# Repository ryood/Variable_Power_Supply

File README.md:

Variable_Power_Supply
=====================

両電源の可変電圧電源
電流電圧計付き

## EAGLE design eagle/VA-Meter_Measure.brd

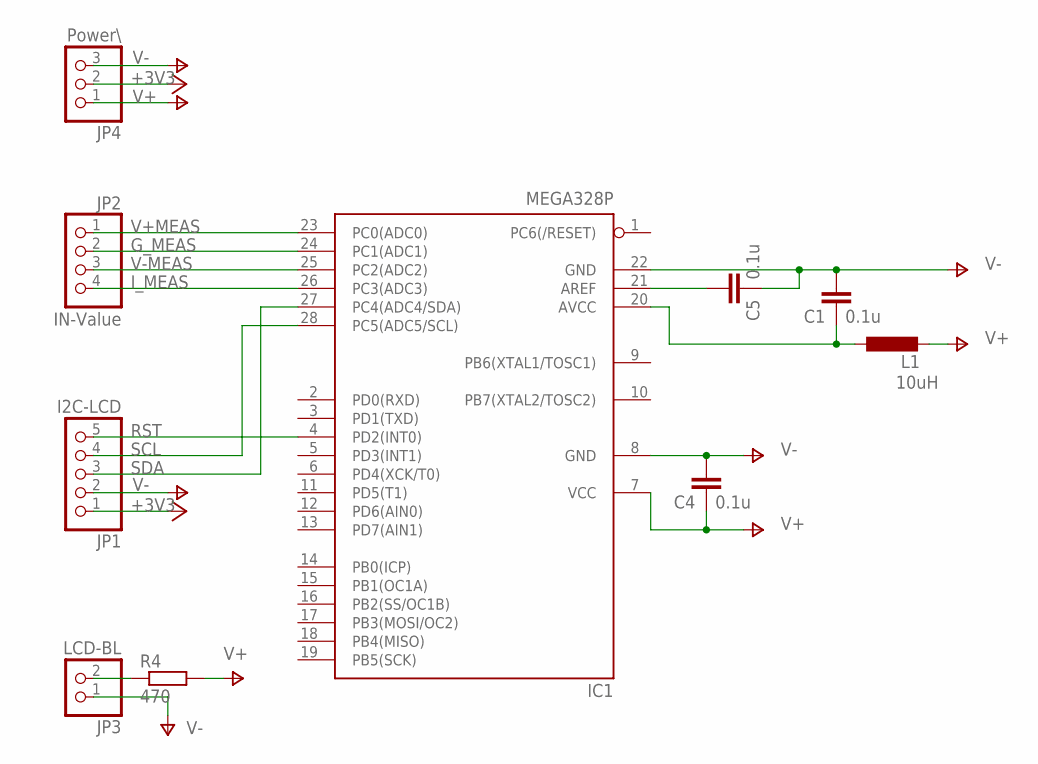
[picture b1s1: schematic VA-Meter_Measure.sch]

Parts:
C1, C4, C5: 0.1u; C050-024X044
IC1: MEGA328P
JP1: I2C-LCD; 1X05
JP2: IN-Value; 1X04
JP3: LCD-BL; 1X02
JP4: Power\; 1X03
L1: 10uH; 6000-XXXX-RC
R4: 470; 0207/7

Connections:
+3V3: JP1.1, JP4.2
G_MEAS: IC1.24 (PC1(ADC1)), JP2.2
I_MEAS: IC1.26 (PC3(ADC3)), JP2.4
unnamed: JP3.2, R4.1
unnamed: C5.2, IC1.21 (AREF)
unnamed: C1.1, IC1.20 (AVCC), L1.1
RST: IC1.4 (PD2(INT0)), JP1.5
SCL: IC1.28 (PC5(ADC5/SCL)), JP1.4
SDA: IC1.27 (PC4(ADC4/SDA)), JP1.3
V+: C4.1, IC1.7 (VCC), JP4.1, L1.2, R4.2
V+MEAS: IC1.23 (PC0(ADC0)), JP2.1
V-: C1.2, C4.2, C5.1, IC1.8 (GND), IC1.22 (GND), JP1.2, JP3.1, JP4.3
V-MEAS: IC1.25 (PC2(ADC2)), JP2.3

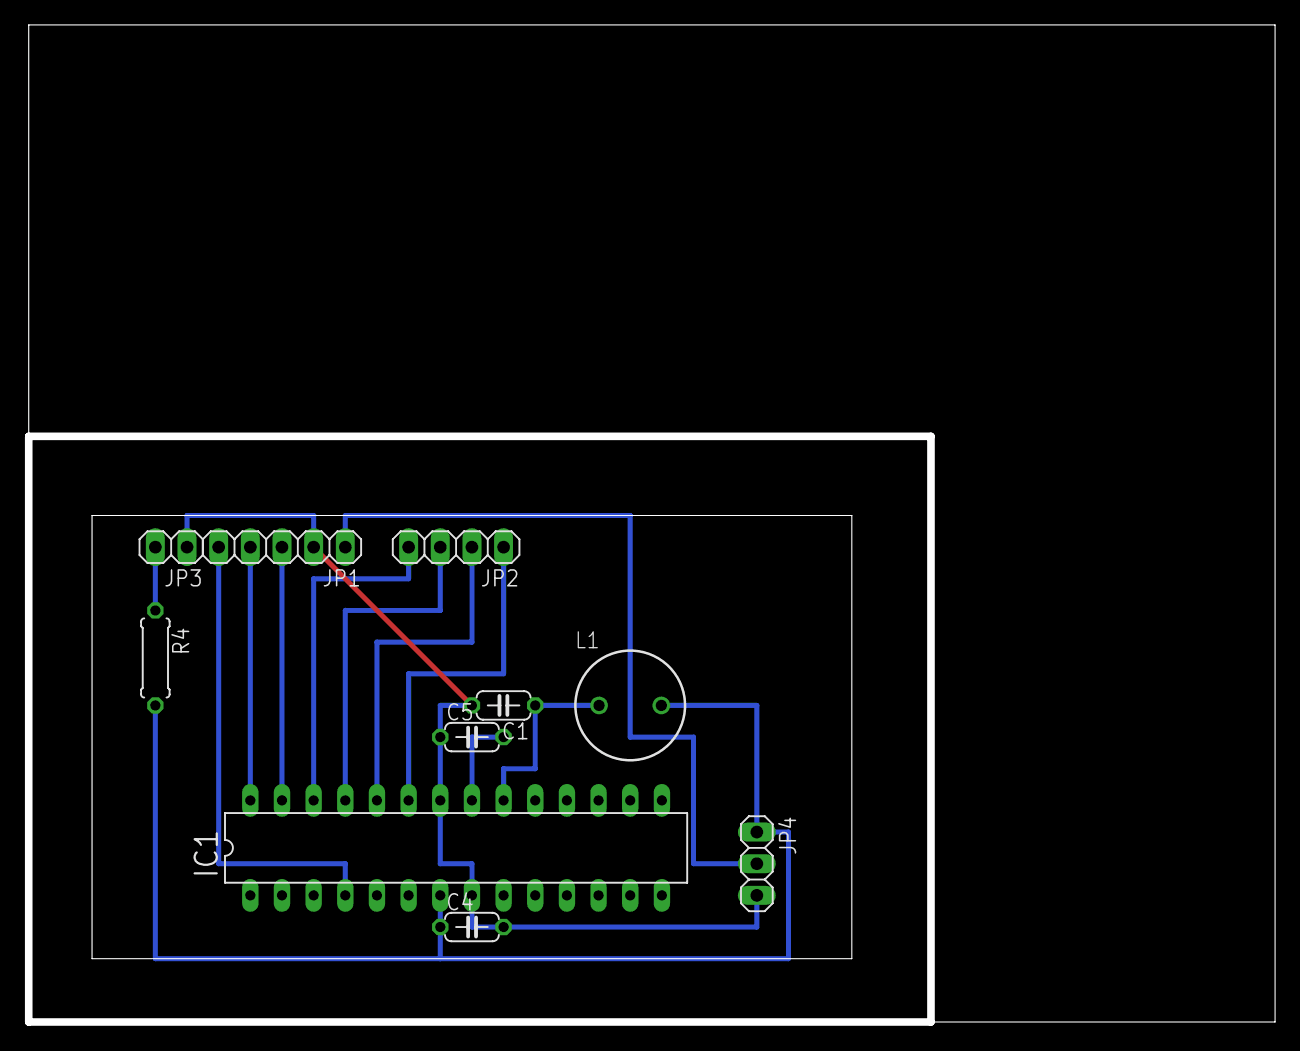
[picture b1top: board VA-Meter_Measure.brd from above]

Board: 2 copper layers, 100.0 x 80.0 mm, 10 parts (0 on the bottom side), 13 nets.

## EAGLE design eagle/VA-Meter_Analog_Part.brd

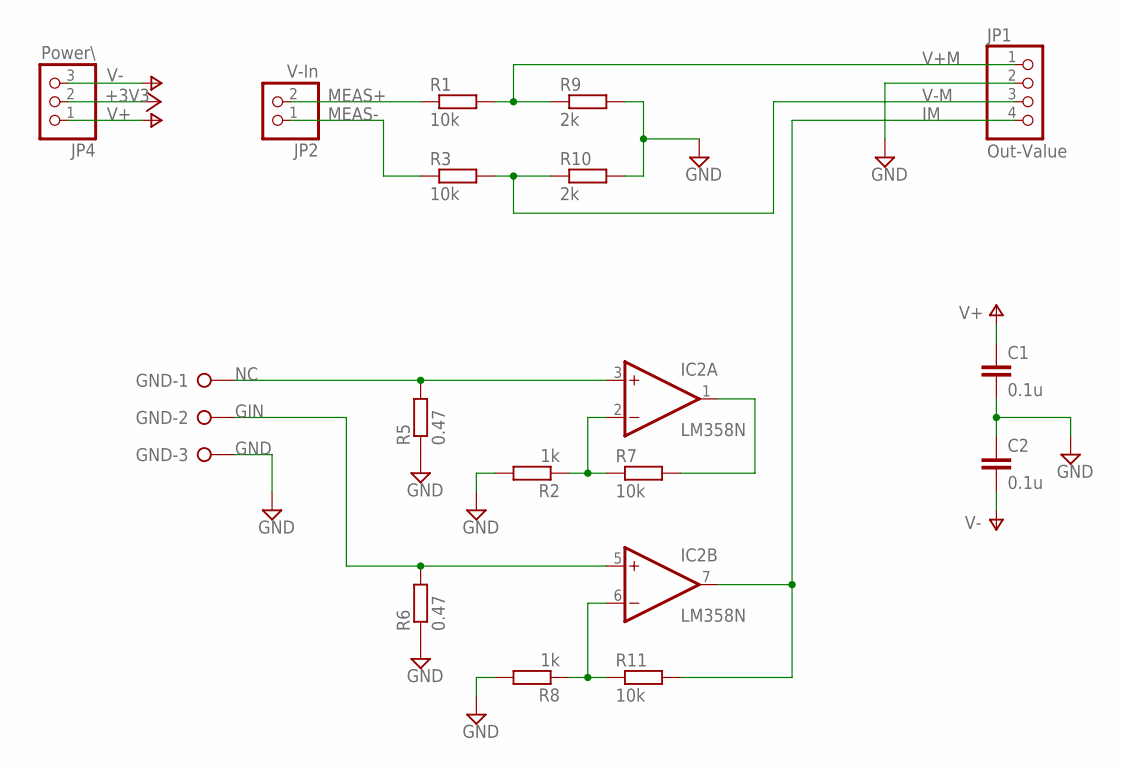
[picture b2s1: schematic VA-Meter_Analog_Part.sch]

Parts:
C1, C2: 0.1u; C050-024X044
GND: W237-03P; W237-133
IC2: LM358N; DIL08
JP1: Out-Value; 1X04
JP2: V-In; 1X02
JP4: Power\; 1X03
R1, R3, R7, R11: 10k; 0207/7
R2, R8: 1k; 0207/7
R5, R6: 0.47; P0613/15
R9, R10: 2k; 0207/7

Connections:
+3V3: JP4.2
GIN: GND.2, IC2.5 (+IN), R6.2
GND: C1.2, C2.1, GND.3, JP1.2, R2.2, R5.1, R6.1, R8.2, R9.2, R10.2
IM: IC2.7 (OUT), JP1.4, R11.2
MEAS+: JP2.2, R1.1
MEAS-: JP2.1, R3.1
unnamed: IC2.1 (OUT), R7.2
unnamed: IC2.2 (-IN), R2.1, R7.1
unnamed: IC2.6 (-IN), R8.1, R11.1
NC: GND.1, IC2.3 (+IN), R5.2
V+: C1.1, IC2.8 (V+), JP4.1
V+M: JP1.1, R1.2, R9.1
V-: C2.2, IC2.4 (V-), JP4.3
V-M: JP1.3, R3.2, R10.1

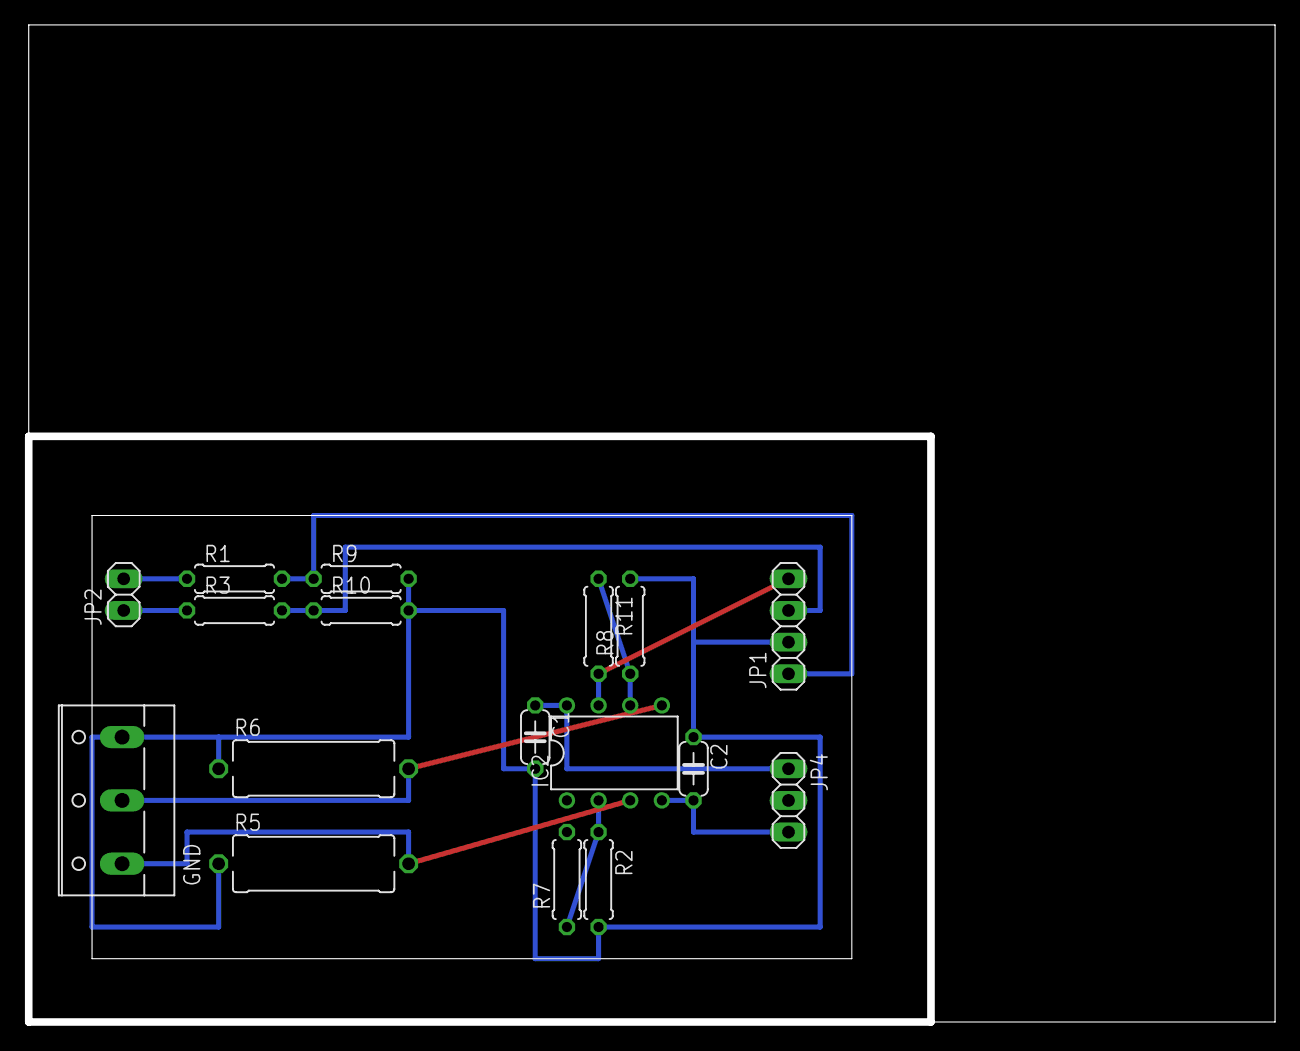
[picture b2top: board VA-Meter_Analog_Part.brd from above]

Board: 2 copper layers, 100.0 x 80.0 mm, 17 parts (0 on the bottom side), 13 nets.

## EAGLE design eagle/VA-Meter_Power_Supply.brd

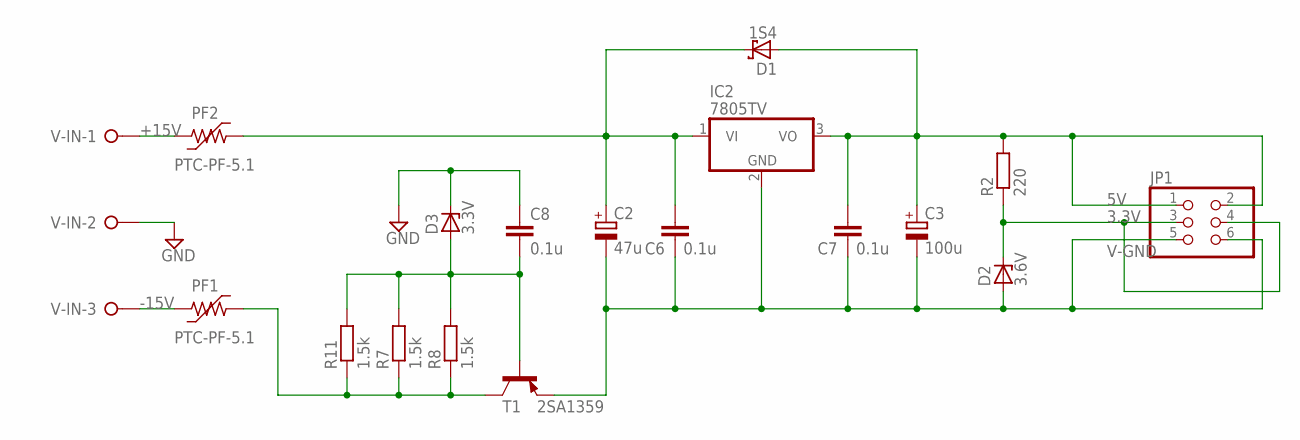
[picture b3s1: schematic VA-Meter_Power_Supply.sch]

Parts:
C2: 47u; E2,5-5
C3: 100u; E2,5-6
C6, C7, C8: 0.1u; C050-024X044
D1: 1S4; DO35-7
D2: 3.6V; ZDIO-5
D3: 3.3V; ZDIO-5
IC2: 7805TV; TO220V
JP1: PINHD-2X3; 2X03
PF1, PF2: PTC-PF-5.1; PF-5.1
R2: 220; 0204/7
R7, R8, R11: 1.5k; 0207/7
T1: 2SA1359; TO126V
V-IN: W237-03P; W237-133

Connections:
3.3V: D2.C, JP1.3, JP1.4, R2.1
5V: C3.+, C7.2, D1.A, IC2.3 (VO), JP1.1, JP1.2, R2.2
+15V: C2.+, C6.2, D1.C, IC2.1 (VI), PF2.2
-15V: PF1.2, R7.1, R8.1, R11.1, T1.2 (C)
GND: C8.1, D3.C, V-IN.2
unnamed: C8.2, D3.A, R7.2, R8.2, R11.2, T1.3 (B)
unnamed: PF2.1, V-IN.1
unnamed: PF1.1, V-IN.3
V-GND: C2.-, C3.-, C6.1, C7.1, D2.A, IC2.2 (GND), JP1.5, JP1.6, T1.1 (E)

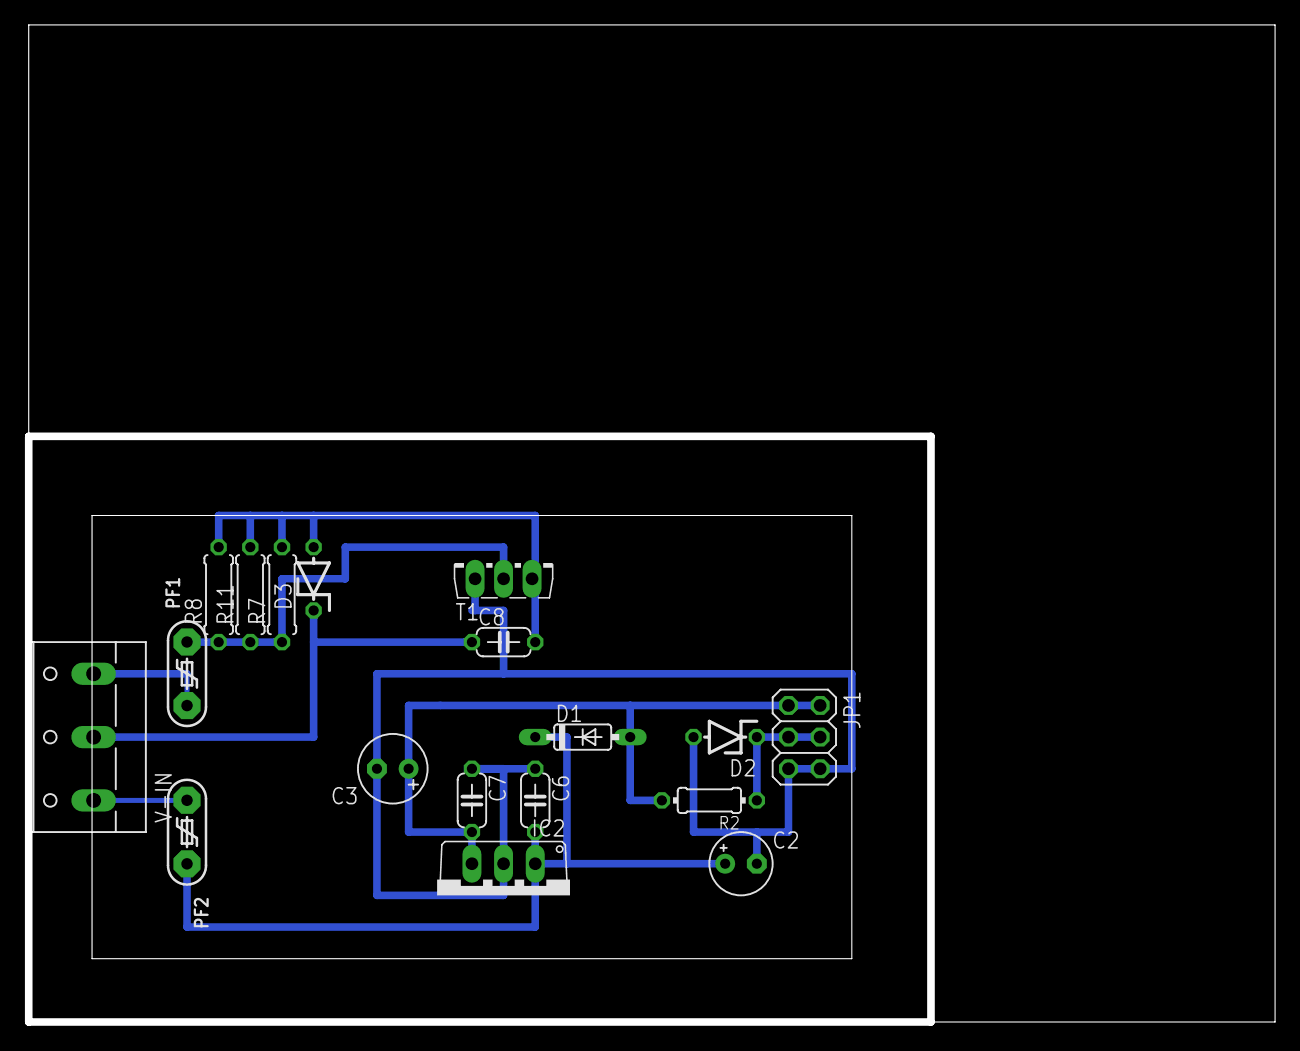
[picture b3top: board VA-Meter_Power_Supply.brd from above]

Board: 2 copper layers, 100.0 x 80.0 mm, 18 parts (0 on the bottom side), 9 nets.

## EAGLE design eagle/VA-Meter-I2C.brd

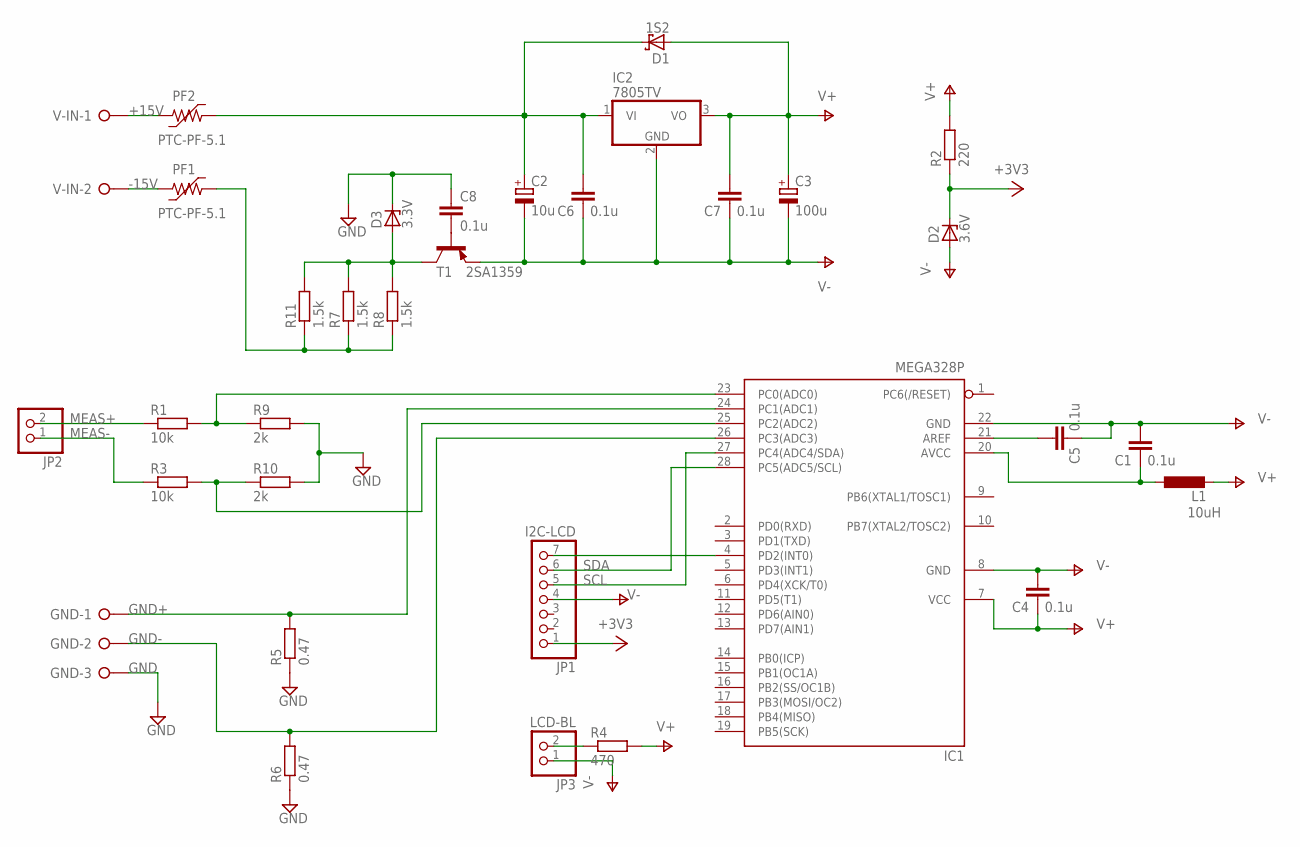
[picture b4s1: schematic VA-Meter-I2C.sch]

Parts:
C1, C4, C5, C6, C7, C8: 0.1u; C050-024X044
C2: 10u; E2,5-5
C3: 100u; E2,5-6
D1: 1S2; CB417-15
D2: 3.6V; ZDIO-5
D3: 3.3V; ZDIO-5
GND: W237-03P; W237-133
IC1: MEGA328P
IC2: 7805TV; TO220V
JP1: I2C-LCD; 1X07
JP2: PINHD-1X2; 1X02
JP3: LCD-BL; 1X02
L1: 10uH; 6000-XXXX-RC
PF1, PF2: PTC-PF-5.1; PF-5.1
R1, R3: 10k; 0207/7
R2: 220; 0207/7
R4: 470; 0207/7
R5, R6: 0.47; P0613/15
R7, R8, R11: 1.5k; P0613/15
R9, R10: 2k; 0207/7
T1: 2SA1359; TO126V
V-IN: W237-02P; W237-132

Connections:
+3V3: D2.C, JP1.1, R2.1
+15V: C2.+, C6.2, D1.C, IC2.1 (VI), PF2.2
-15V: PF1.2, R7.1, R8.1, R11.1
GND: C8.1, D3.C, GND.3, R5.1, R6.1, R9.2, R10.2
GND+: GND.1, IC1.24 (PC1(ADC1)), R5.2
GND-: GND.2, IC1.26 (PC3(ADC3)), R6.2
MEAS+: JP2.2, R1.1
MEAS-: JP2.1, R3.1
unnamed: D3.A, R7.2, R8.2, R11.2, T1.2 (C)
unnamed: JP3.2, R4.1
unnamed: IC1.23 (PC0(ADC0)), R1.2, R9.1
unnamed: IC1.25 (PC2(ADC2)), R3.2, R10.1
unnamed: C8.2, T1.3 (B)
unnamed: PF2.1, V-IN.1
unnamed: PF1.1, V-IN.2
unnamed: C5.2, IC1.21 (AREF)
unnamed: C1.1, IC1.20 (AVCC), L1.1
unnamed: IC1.4 (PD2(INT0)), JP1.7
SCL: IC1.27 (PC4(ADC4/SDA)), JP1.5
SDA: IC1.28 (PC5(ADC5/SCL)), JP1.6
V+: C3.+, C4.1, C7.2, D1.A, IC1.7 (VCC), IC2.3 (VO), L1.2, R2.2, R4.2
V-: C1.2, C2.-, C3.-, C4.2, C5.1, C6.1, C7.1, D2.A, IC1.8 (GND), IC1.22 (GND), IC2.2 (GND), JP1.4, JP3.1, T1.1 (E)

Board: 2 copper layers, 33 parts (0 on the bottom side), 22 nets, no tracks yet.

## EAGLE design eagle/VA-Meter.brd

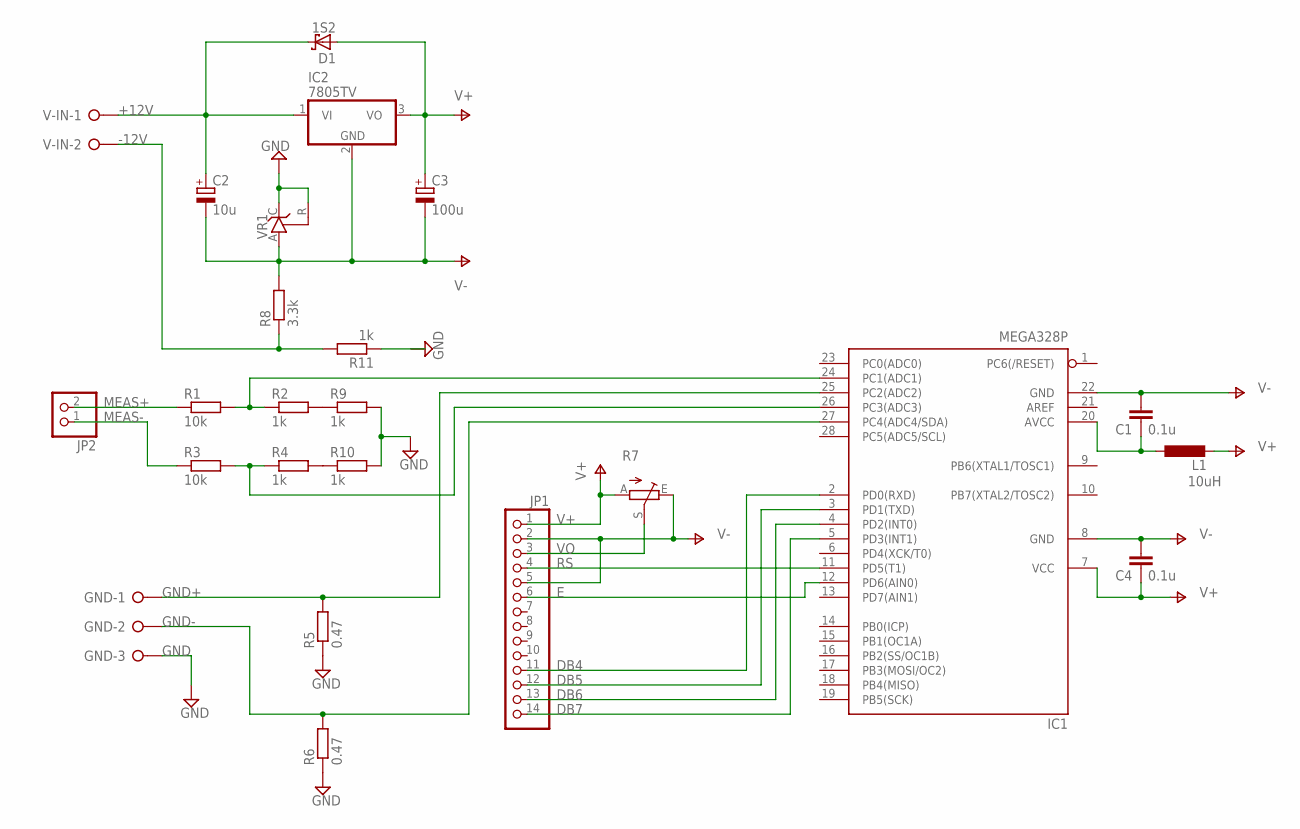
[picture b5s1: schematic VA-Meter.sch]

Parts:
C1, C4: 0.1u; C050-024X044
C2: 10u; E2,5-5
C3: 100u; E2,5-6
D1: 1S2; CB417-15
GND: W237-03P; W237-133
IC1: MEGA328P
IC2: 7805TV; TO220V
JP1: PINHD-1X14; 1X14
JP2: PINHD-1X2; 1X02
L1: 10uH; 6000-XXXX-RC
R1, R3: 10k; 0207/7
R2, R4, R9, R10: 1k; 0207/7
R5, R6: 0.47; P0613/15
R7: TRIM_EU-B25P; B25P
R8: 3.3k; P0613/15
R11: 1k; P0613/15
V-IN: W237-02P; W237-132
VR1: TL431CLP; TO92-CLP

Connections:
+12V: C2.+, D1.C, IC2.1 (VI), V-IN.1
-12V: R8.1, R11.2, V-IN.2
DB4: IC1.2 (PD0(RXD)), JP1.11
DB5: IC1.3 (PD1(TXD)), JP1.12
DB6: IC1.4 (PD2(INT0)), JP1.13
DB7: IC1.5 (PD3(INT1)), JP1.14
E: IC1.12 (PD6(AIN0)), JP1.6
GND: GND.3, R5.1, R6.1, R9.2, R10.2, VR1.C, VR1.R
GND+: GND.1, IC1.25 (PC2(ADC2)), R5.2
GND-: GND.2, IC1.27 (PC4(ADC4/SDA)), R6.2
MEAS+: JP2.2, R1.1
MEAS-: JP2.1, R3.1
unnamed: IC1.24 (PC1(ADC1)), R1.2, R2.1
unnamed: IC1.26 (PC3(ADC3)), R3.2, R4.1
unnamed: R2.2, R9.1
unnamed: C1.1, IC1.20 (AVCC), L1.1
unnamed: R4.2, R10.1
RS: IC1.11 (PD5(T1)), JP1.4
V+: C3.+, C4.1, D1.A, IC1.7 (VCC), IC2.3 (VO), JP1.1, L1.2, R7.A
V-: C1.2, C2.-, C3.-, C4.2, IC1.8 (GND), IC1.22 (GND), IC2.2 (GND), JP1.2, JP1.5, R7.E, R8.2, VR1.A
VO: JP1.3, R7.S

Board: 2 copper layers, 24 parts (0 on the bottom side), 21 nets, no tracks yet.

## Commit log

2014-09-07 Commit Atmel Studio VAMeter project
2014-09-07 VAMeterを2入力に修正 ブレッドボード配線図のGND線を修正
2014-09-09 負電源用に反転アンプを追加
2014-09-14 ブレッドボード・デザイン修正
2014-09-26 テスト用ファイルを追加
2014-09-26 テスト用画像を追加
2014-10-04 I2Cレベルシフト 2SC1815の修正
2014-10-06 回路図を追加
2014-10-06 回路図を修正 シャントレギュレータの接続
2014-10-08 VA-MeterのFritzingを追加
2014-10-08 ブレッドボードの配線図を修正
2014-10-13 回路図修正
2014-10-13 ブレッドボード図追加 I2Cレベルシフト 三端子レギュレータ７８０５
2014-10-13 I2CレベルシフトIC PCA9306のブレッドボード図を追加
2014-10-16 VA-Meter-I2C 回路図追加
2014-10-16 aitendo I2C LCD ブレッドボード図追加
2014-10-16 AtmelStudio DualVAMeterプロジェクト追加
2014-10-19 DualVAMeter.c 修正 SPLC792-I2C-2 ブレッドボード図修正
2014-10-19 DualVAMeter.cproj プロジェクトファイル追加
2014-10-19 DualVAMeter.c LCD表示、ADC、まあまあOK
2014-10-19 DualVAMeter.c テスト用に修正
2014-10-19 I2C-LCD 回路図を修正
2014-10-19 7805+Zenerのブレッドボード図を追加
2014-10-19 V-Meter-I2C 回路図修正 シャントレギュレータ－ではなくAVCCを基準電圧に
2014-10-22 DualVAMeter.c テスト用に即値を表示(0..1023)
2014-10-24 分圧回路、SPLC792-I2C＆AVR ADCブレッドボード図追加
2014-10-24 7805+Zener ブレッドボード図、部品のスペースを変更
2014-10-24 7805+Zener ブレッドボード図修正
2014-10-26 Zener定電圧回路 LTSpiceシミュレーションを追加
2014-10-26 7805+Zenar.fzz 測定用電源部のGNDシフトをZenerに変更
2014-10-29 7805を使った測定部の電源のシミュレーションを追加
2014-10-29 7805+Zenerのブレッドボード図を修正
2014-10-31 電源部の保護回路を±のポリスイッチに変更
2014-11-02 Power Supply 回路図、基板図追加
2014-11-02 結合テストExcel表追加
2014-11-02 Power Supply 回路図、基板図修正
2014-11-02 アナログ部 VA-Meter_Analog_Part 回路図、基板図追加
2014-11-02 VA-Meter_Measure 測定部の回路図、基板図を追加
2014-11-02 VA-Meter_Power_Supply 測定部電源の回路図、基板図修正 入力端子にGNDを追加
2014-11-05 VA-Meter_Power_Supply.brd 測定部の電源 基板図の修正 放熱器の塗りつぶしをハッシュに
2014-11-05 VA-Meter_Power_Supply.brd 測定部の電源、基板設計図修正、ジャンパをなしに
2014-11-05 VA-Meter_Power_Supply 回路図の電解コンデンサの値を47uFに変更
2014-11-08 VA-Meter_Power_Supply 2SA1359の定電圧源の回路が間違っていたので修正
2014-11-08 VA-Meter_Measure 回路図、SCLとSDAの信号線の名前が逆だったのを修正
2014-11-08 VA-Meter_Power_Supply 基板図をジャンパを使わないように修正
2014-11-08 7805+Zenner.fzz ブレッドボード図の配線が間違っていたので修正
2014-11-10 VA-Meter_Measure 電流電圧計デジタル部基板図修正
2014-11-10 測定部電源テスト表、測定部デジタル部テスト表を追加
2014-11-13 測定部デジタル部テスト表更新 電源、AVR、LCDありを追加
2014-11-13 Integration-Test.fzz アナログ部のテスト用のブレッドボード図を追加
2014-11-16 Integration-Test.fzz 結合テストブレッドボード図修正
2014-11-16 結合テスト結果20141115.xlsx追加
2014-11-16 結合テスト結果20141115.xlsx修正
2014-11-16 アナログ部の修正 電流値の増幅を11倍に変更
2014-11-24 ユニバーサル基板結合テスト20141122.xlsx 測定部アナログ部テスト.xlsx 追加
2014-11-24 Connection-Test.fzz ユニバーサル基板結合テスト用結線図追加
2014-11-24 ユニバーサル基板結合テスト ブレッドボード図修正 正負GNDをまとめた
2014-11-24 VA-Meter_Analog_Part 回路図、基板図、電流値を一つにまとめてGND値を出力するように変更 アナログ部テスト 更新
2014-11-24 ユニバーサル基板結合テスト20141124.xlsx GND値を計測するようにして結合テスト結果を追加
2014-11-27 ユニバーサル基板結合テスト20141124.xlsx 更新
2014-11-27 MB-6S.dwg ケース加工図追加
2014-11-30 ケース加工図修正 OUTPUTスイッチを追加、POWERスイッチを背面に
2014-11-30 Connection.fzz 結線図を追加
2014-11-30 ケース加工図修正 基板位置、角穴用ガイド
2014-11-30 ケース加工図修正
2014-12-03 MB-6S.dwg ケース加工図を修正 DINジャックの固定用ネジ穴を追加
2014-12-09 Connection.fzz 結線図修正 デジタル部の電源コネクタを修正
2014-12-12 VA-Meter_Measure.sch デジタル部回路図修正 入力端子名の変更
2014-12-12 LCD読み取り値テスト結果追加
2014-12-18 firmwareを電圧・電流、GND値を表示するように変更
2014-12-18 firmware 表示系のバグを修正
2014-12-18 ケース内配線図 微修正

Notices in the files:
parts and their libraries:
polyswitch: Copyright (C) 2008, Bob Starr
